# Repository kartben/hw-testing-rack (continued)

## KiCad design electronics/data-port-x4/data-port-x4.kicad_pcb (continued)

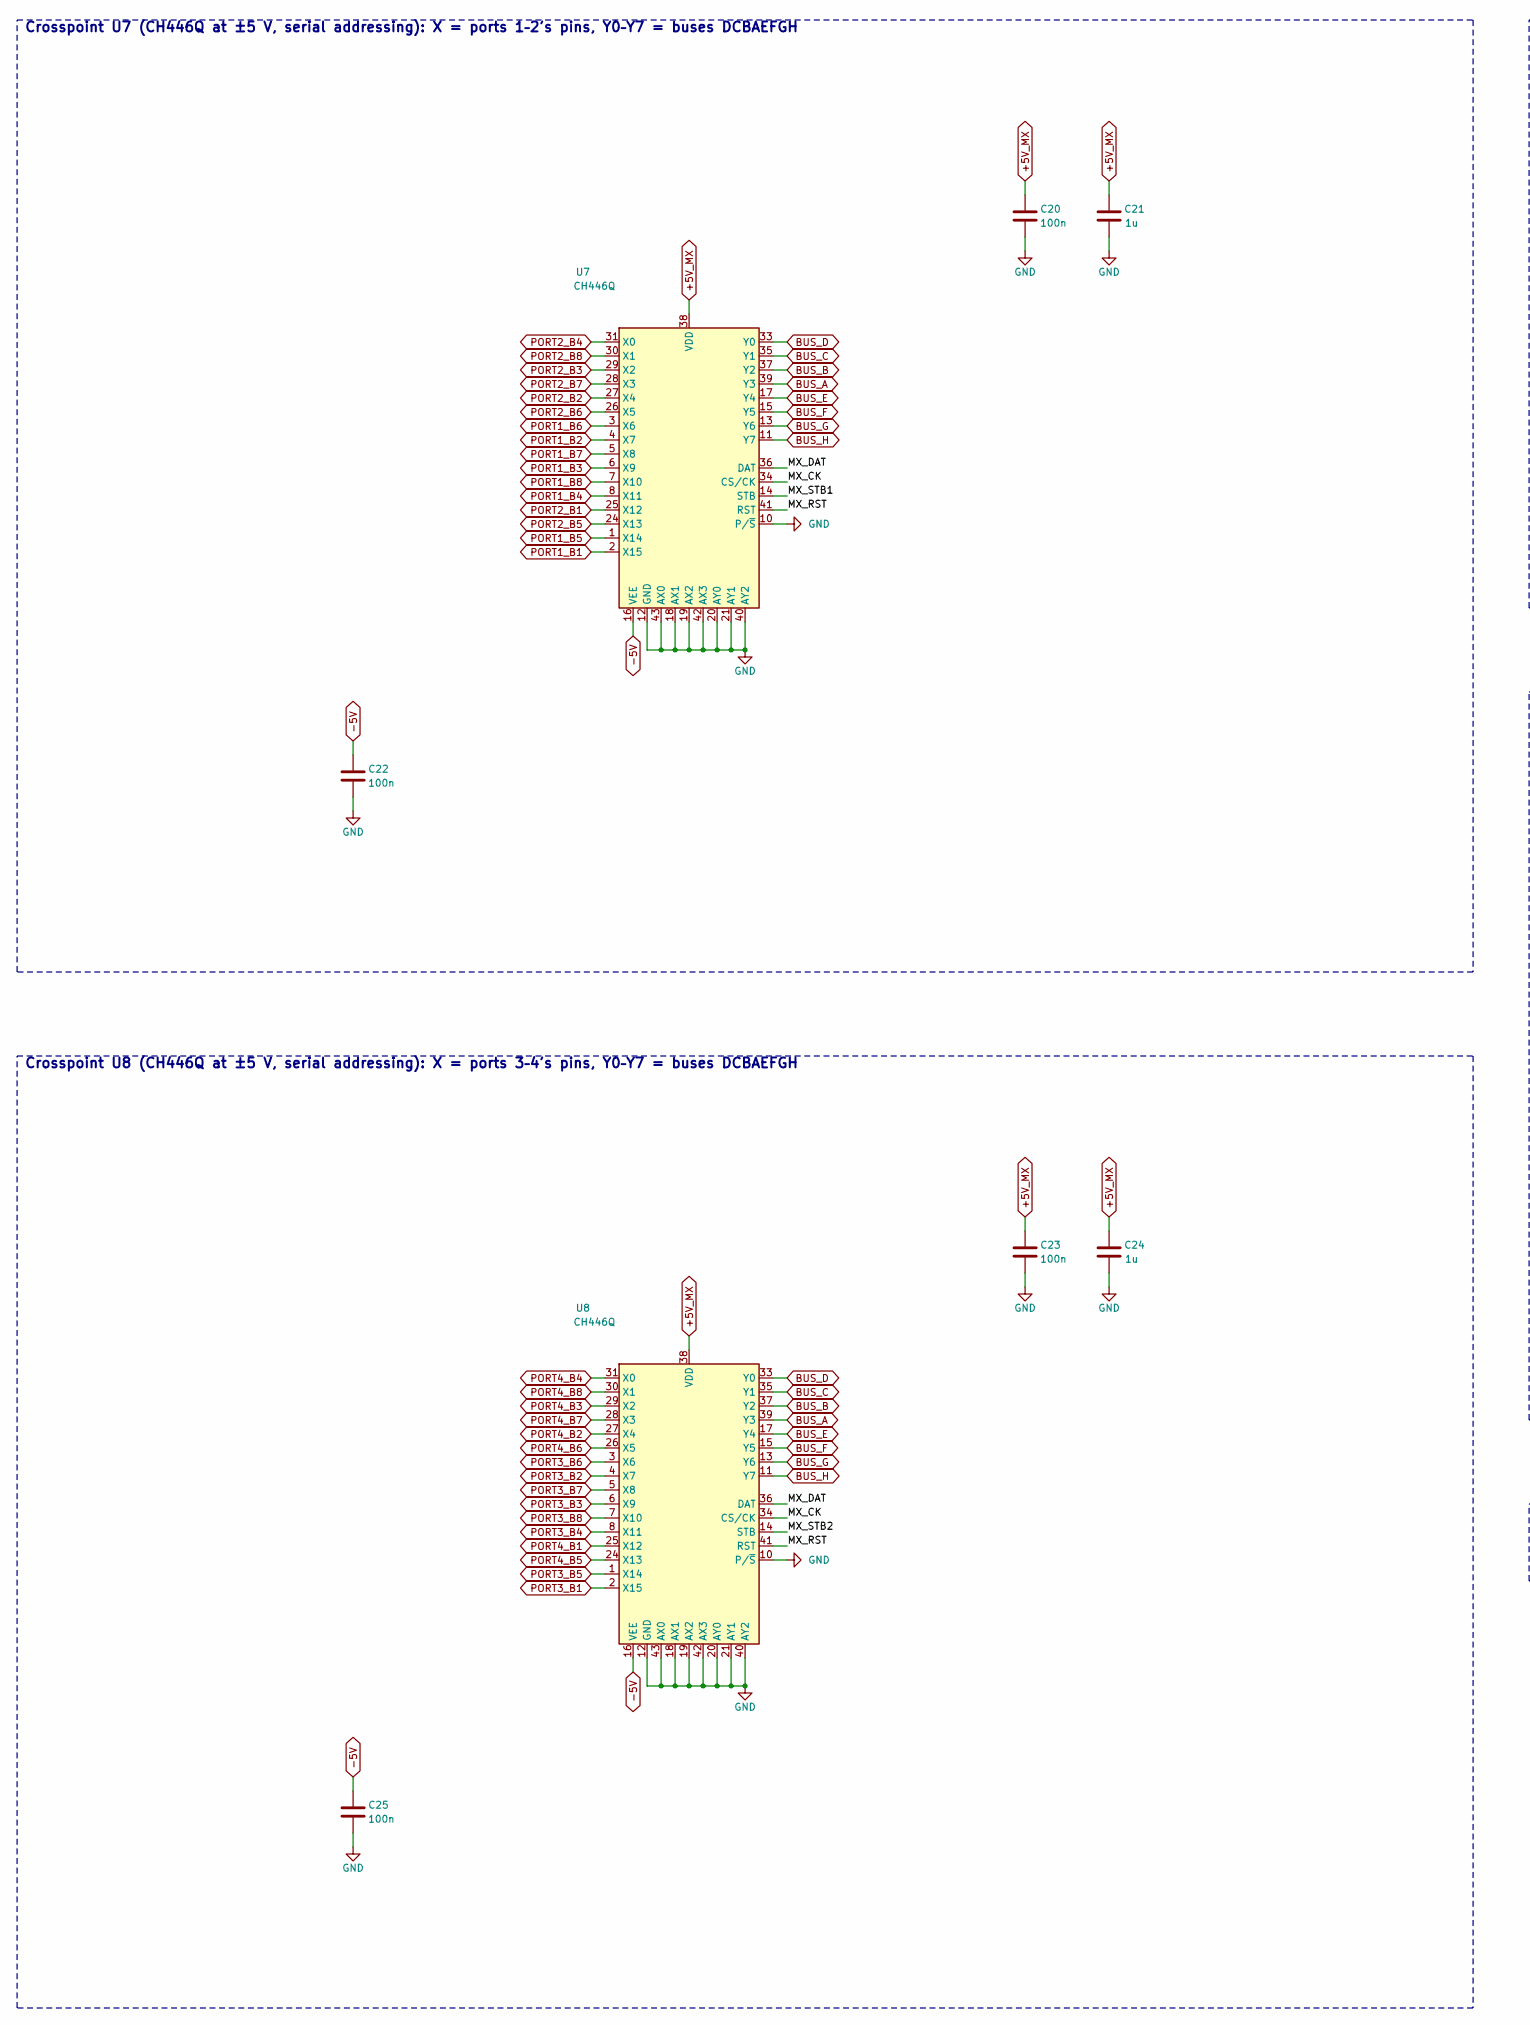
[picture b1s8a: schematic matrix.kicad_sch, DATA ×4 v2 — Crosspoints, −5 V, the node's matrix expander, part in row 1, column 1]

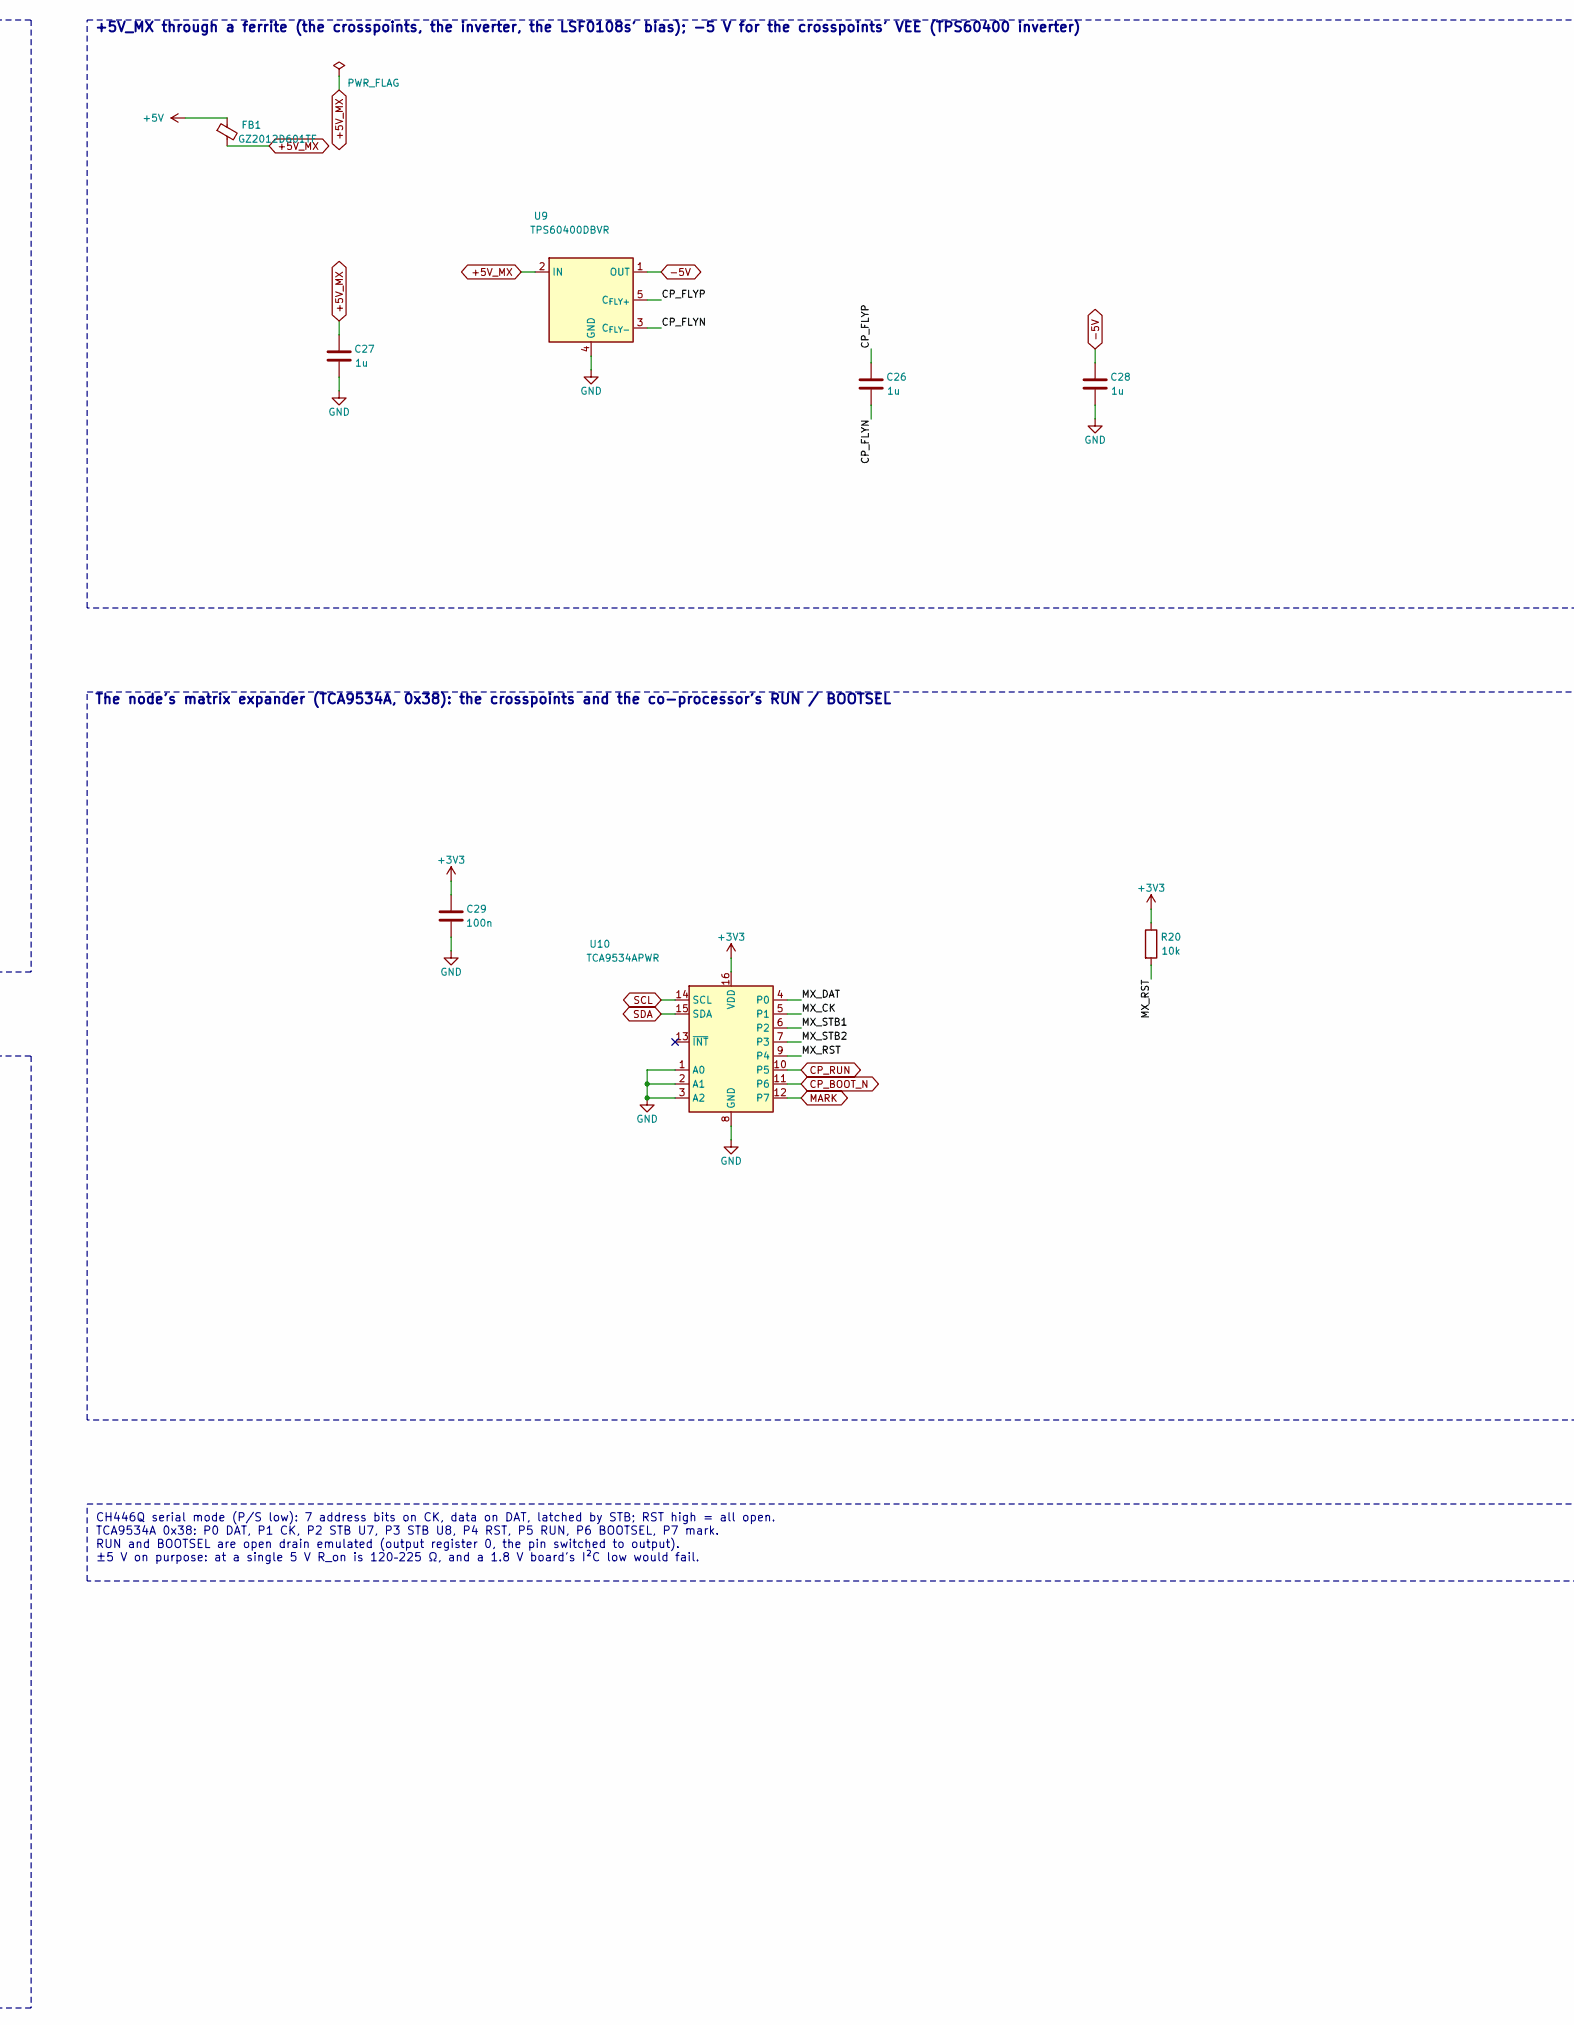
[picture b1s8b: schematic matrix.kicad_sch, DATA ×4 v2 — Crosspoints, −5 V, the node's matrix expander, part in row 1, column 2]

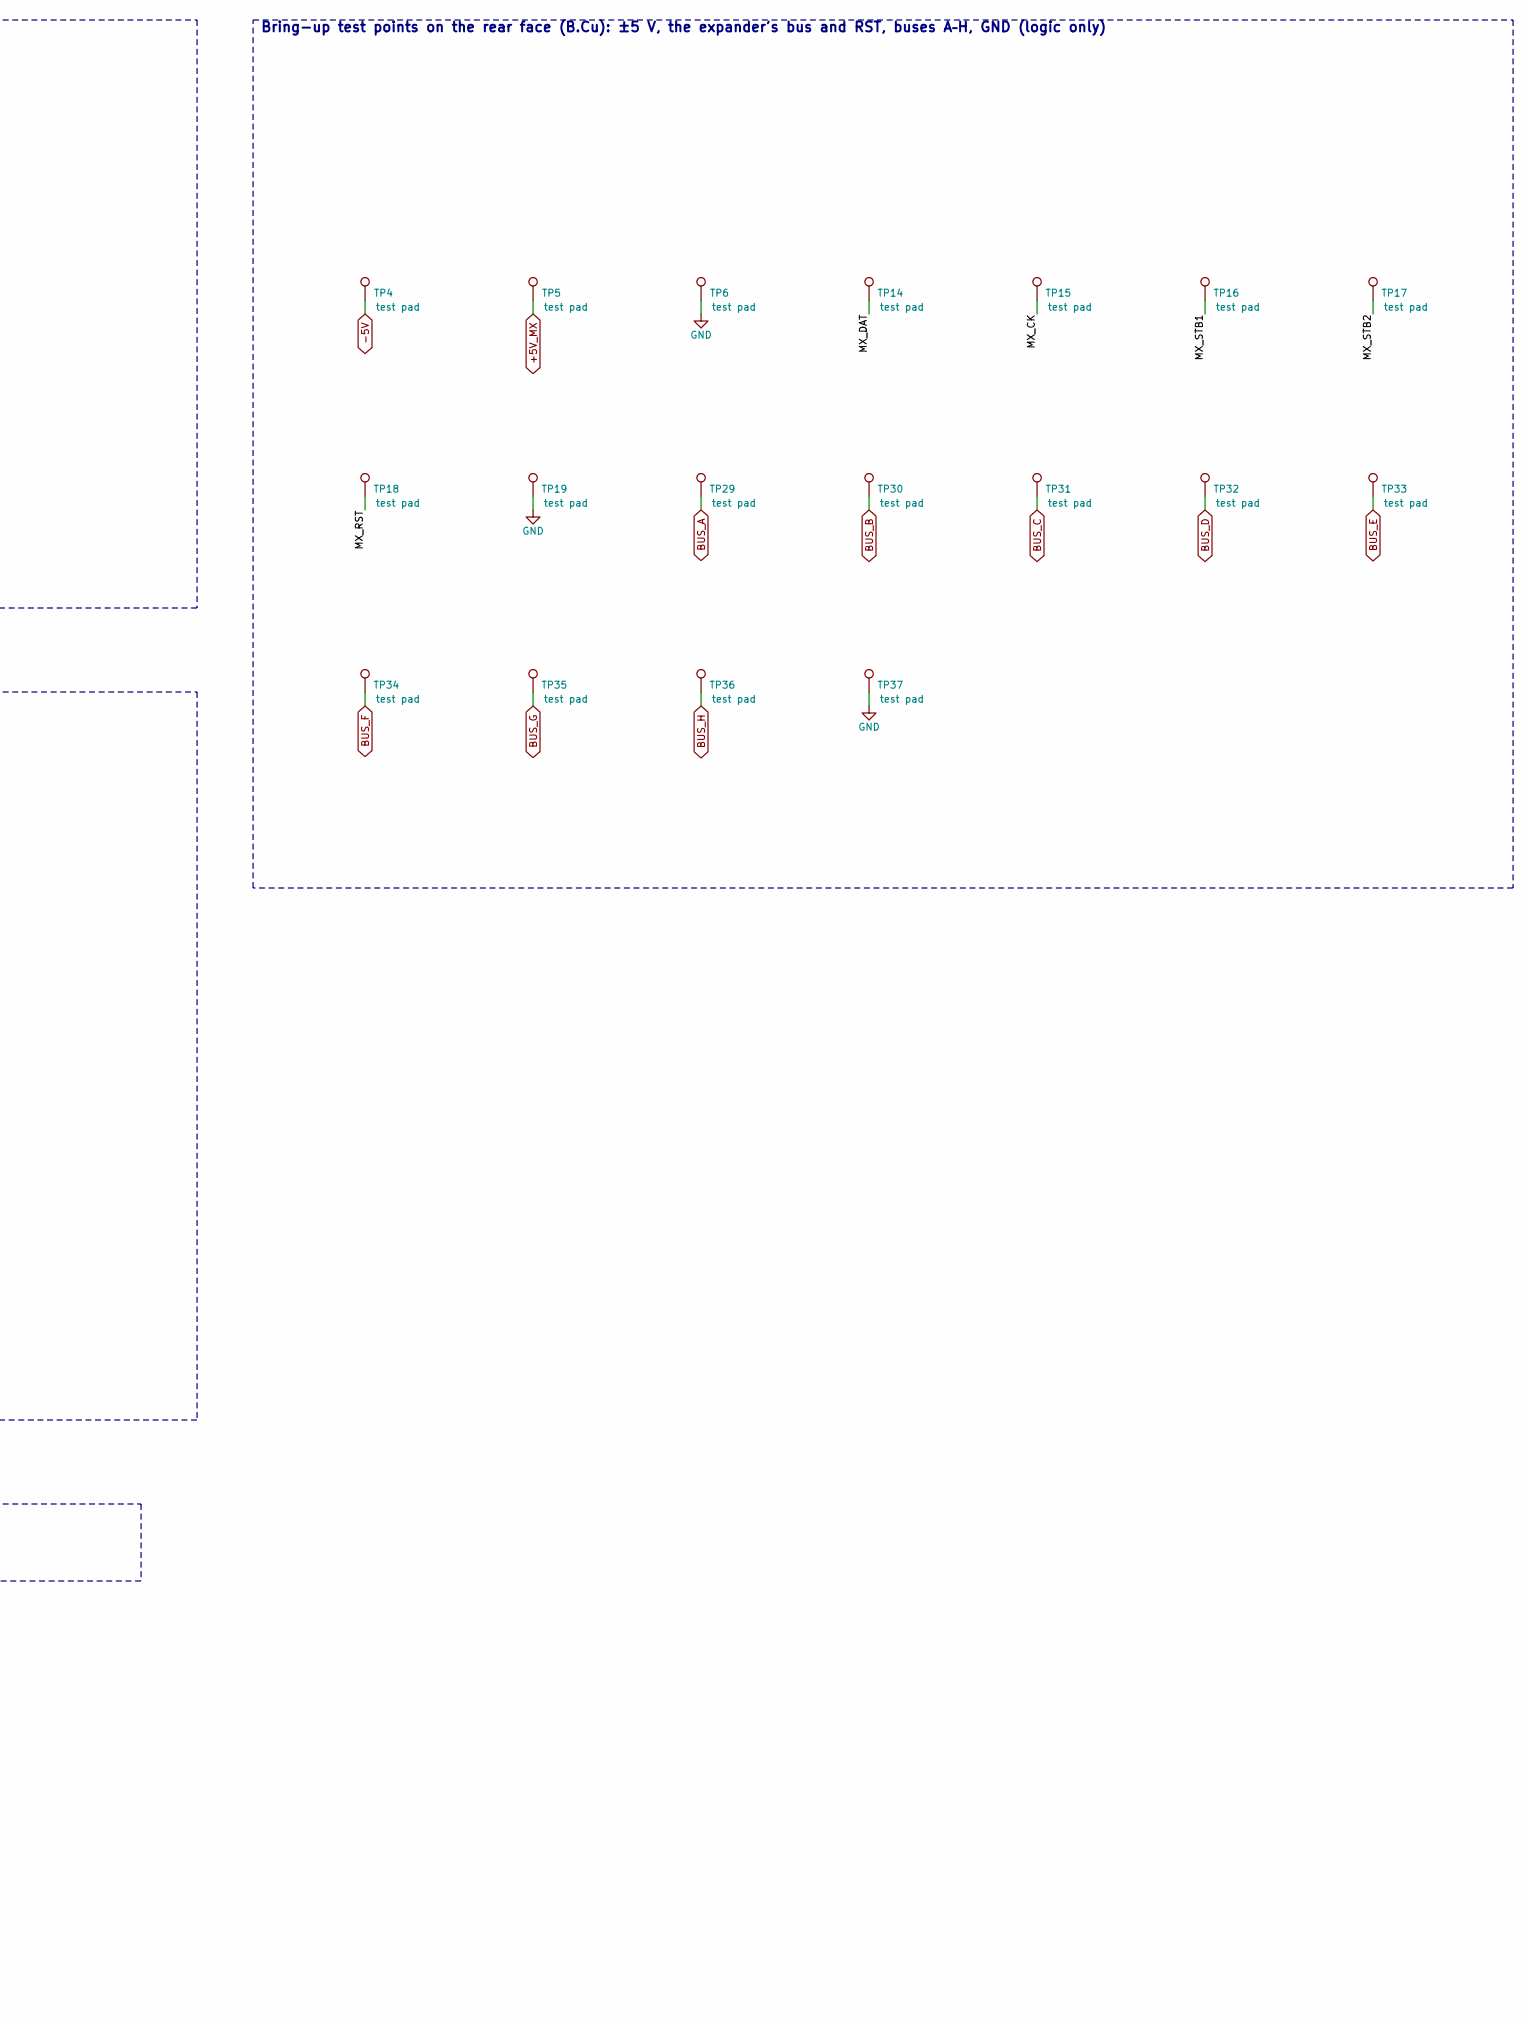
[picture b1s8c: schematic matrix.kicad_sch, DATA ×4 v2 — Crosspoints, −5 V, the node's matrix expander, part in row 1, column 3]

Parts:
C20, C22, C23, C25, C29: 100n; C_0402_1005Metric; MPN CL05B104KO5NNNC; LCSC C1525
C21, C24, C26, C27, C28: 1u; C_0402_1005Metric; MPN CL05A105KA5NQNC; LCSC C52923
FB1: GZ2012D601TF; L_0805_2012Metric; MPN GZ2012D601TF; LCSC C1017
R20: 10k; R_0402_1005Metric; MPN 0402WGF1002TCE; LCSC C25744
TP4, TP5, TP6, TP19, TP37: test pad; TestPoint_Pad_D1.5mm; MPN test pad
TP14, TP15, TP16, TP17, TP18, TP29, TP30, TP31, TP32, TP33, TP34, TP35, TP36: test pad; TestPoint_Pad_D1.0mm; MPN test pad
U7, U8: CH446Q; LQFP-44_10x10mm_P0.8mm; MPN CH446Q; LCSC C109471
U9: TPS60400DBVR; SOT-23-5; MPN TPS60400DBVR; LCSC C9839
U10: TCA9534APWR; TSSOP-16_4.4x5mm_P0.65mm; MPN TCA9534APWR; LCSC C206010

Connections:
+3V3: C29.1, R20.1, U10.16 (VDD); also elsewhere on the board
+5V: FB1.1; also elsewhere on the board
+5V_MX: C20.1, C21.1, C23.1, C24.1, C27.1, FB1.2, TP5.1, U7.38 (VDD), U8.38 (VDD), U9.2 (IN); also elsewhere on the board
-5V: C22.1, C25.1, C28.1, TP4.1, U7.16 (VEE), U8.16 (VEE), U9.1 (OUT); also elsewhere on the board
/Matrix/CP_FLYN: C26.2, U9.3 (C_{FLY-})
/Matrix/CP_FLYP: C26.1, U9.5 (C_{FLY+})
/Matrix/MX_CK: TP15.1, U7.34 (CS/CK), U8.34 (CS/CK), U10.5 (P1)
/Matrix/MX_DAT: TP14.1, U7.36 (DAT), U8.36 (DAT), U10.4 (P0)
/Matrix/MX_RST: R20.2, TP18.1, U7.41 (RST), U8.41 (RST), U10.9 (P4)
/Matrix/MX_STB1: TP16.1, U7.14 (STB), U10.6 (P2)
/Matrix/MX_STB2: TP17.1, U8.14 (STB), U10.7 (P3)
BUS_A: TP29.1, U7.39 (Y3), U8.39 (Y3); also elsewhere on the board
BUS_B: TP30.1, U7.37 (Y2), U8.37 (Y2); also elsewhere on the board
BUS_C: TP31.1, U7.35 (Y1), U8.35 (Y1); also elsewhere on the board
BUS_D: TP32.1, U7.33 (Y0), U8.33 (Y0); also elsewhere on the board
BUS_E: TP33.1, U7.17 (Y4), U8.17 (Y4); also elsewhere on the board
BUS_F: TP34.1, U7.15 (Y5), U8.15 (Y5); also elsewhere on the board
BUS_G: TP35.1, U7.13 (Y6), U8.13 (Y6); also elsewhere on the board
BUS_H: TP36.1, U7.11 (Y7), U8.11 (Y7); also elsewhere on the board
CP_BOOT_N: U10.11 (P6); also elsewhere on the board
CP_RUN: U10.10 (P5); also elsewhere on the board
GND: C20.2, C21.2, C22.2, C23.2, C24.2, C25.2, C27.2, C28.2, C29.2, TP6.1, TP19.1, TP37.1, U7.10 (P/~S), U7.12 (GND), U7.18 (AX1), U7.19 (AX2), U7.20 (AY0), U7.21 (AY1), U7.40 (AY2), U7.42 (AX3), U7.43 (AX0), U8.10 (P/~S), U8.12 (GND), U8.18 (AX1), U8.19 (AX2), U8.20 (AY0), U8.21 (AY1), U8.40 (AY2), U8.42 (AX3), U8.43 (AX0), U9.4 (GND), U10.1 (A0), U10.2 (A1), U10.3 (A2), U10.8 (GND); also elsewhere on the board
MARK: U10.12 (P7); also elsewhere on the board
PORT1_B1: U7.2 (X15); also elsewhere on the board
PORT1_B2: U7.4 (X7); also elsewhere on the board
PORT1_B3: U7.6 (X9); also elsewhere on the board
PORT1_B4: U7.8 (X11); also elsewhere on the board
PORT1_B5: U7.1 (X14); also elsewhere on the board
PORT1_B6: U7.3 (X6); also elsewhere on the board
PORT1_B7: U7.5 (X8); also elsewhere on the board
PORT1_B8: U7.7 (X10); also elsewhere on the board
PORT2_B1: U7.25 (X12); also elsewhere on the board
PORT2_B2: U7.27 (X4); also elsewhere on the board
PORT2_B3: U7.29 (X2); also elsewhere on the board
PORT2_B4: U7.31 (X0); also elsewhere on the board
PORT2_B5: U7.24 (X13); also elsewhere on the board
PORT2_B6: U7.26 (X5); also elsewhere on the board
PORT2_B7: U7.28 (X3); also elsewhere on the board
PORT2_B8: U7.30 (X1); also elsewhere on the board
PORT3_B1: U8.2 (X15); also elsewhere on the board
PORT3_B2: U8.4 (X7); also elsewhere on the board
PORT3_B3: U8.6 (X9); also elsewhere on the board
PORT3_B4: U8.8 (X11); also elsewhere on the board
PORT3_B5: U8.1 (X14); also elsewhere on the board
PORT3_B6: U8.3 (X6); also elsewhere on the board
PORT3_B7: U8.5 (X8); also elsewhere on the board
PORT3_B8: U8.7 (X10); also elsewhere on the board
PORT4_B1: U8.25 (X12); also elsewhere on the board
PORT4_B2: U8.27 (X4); also elsewhere on the board
PORT4_B3: U8.29 (X2); also elsewhere on the board
PORT4_B4: U8.31 (X0); also elsewhere on the board
PORT4_B5: U8.24 (X13); also elsewhere on the board
PORT4_B6: U8.26 (X5); also elsewhere on the board
PORT4_B7: U8.28 (X3); also elsewhere on the board
PORT4_B8: U8.30 (X1); also elsewhere on the board
SCL: U10.14 (SCL); also elsewhere on the board
SDA: U10.15 (SDA); also elsewhere on the board

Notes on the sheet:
Crosspoint U7 (CH446Q at ±5 V, serial addressing): X = ports 1–2's pins, Y0–Y7 = buses DCBAEFGH
Crosspoint U8 (CH446Q at ±5 V, serial addressing): X = ports 3–4's pins, Y0–Y7 = buses DCBAEFGH
+5V_MX through a ferrite (the crosspoints, the inverter, the LSF0108s' bias); −5 V for the crosspoints' VEE (TPS60400 inverter)
The node's matrix expander (TCA9534A, 0x38): the crosspoints and the co-processor's RUN / BOOTSEL
Bring-up test points on the rear face (B.Cu): ±5 V, the expander's bus and RST, buses A–H, GND (logic only)
CH446Q serial mode (P/S low): 7 address bits on CK, data on DAT, latched by STB; RST high = all open. TCA9534A 0x38: P0 DAT, P1 CK, P2 STB U7, P3 STB U8, P4 RST, P5 RUN, P6 BOOTSEL, P7 mark. RUN and BOOTSEL are open drain emulated (output register 0, the pin switched to output). ±5 V on purpose: at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

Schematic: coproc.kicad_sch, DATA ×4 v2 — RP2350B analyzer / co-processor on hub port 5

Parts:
C31, C34, C47: 4.7u; C_0402_1005Metric; MPN CL05A475MP5NRNC; LCSC C23733
C32, C33: 4.7u; C_0402_1005Metric_RP; MPN CL05A475MP5NRNC; LCSC C23733
C35, C36, C37, C38, C39, C40, C41, C42, C43, C44, C45, C46: 100n; C_0402_1005Metric; MPN CL05B104KO5NNNC; LCSC C1525
C48, C49: 15p; C_0402_1005Metric; MPN 0402CG150J500NT; LCSC C1548
D1: KT-0805G; LED_0805_2012Metric; MPN KT-0805G; LCSC C2297
FB2: GZ2012D601TF; L_0805_2012Metric; MPN GZ2012D601TF; LCSC C1017
J2: SWD; PinHeader_1x05_P2.54mm_Vertical; MPN HX PZ2.54-1x5P ZZ; LCSC C32713271
L1: AOTA-B201610S3R3-101-T; L_Abracon_AOTA-B201610; MPN AOTA-B201610S3R3-101-T; LCSC C42411119
R21: 33; R_0402_1005Metric; MPN 0402WGF330JTCE; LCSC C25105
R22, R26, R27: 1k; R_0402_1005Metric; MPN 0402WGF1001TCE; LCSC C11702
R23, R24: 27; R_0402_1005Metric; MPN 0402WGF270JTCE; LCSC C25100
R25, R40: 10k; R_0402_1005Metric; MPN 0402WGF1002TCE; LCSC C25744
R38, R41: 100k; R_0402_1005Metric; MPN 0402WGF1003TCE; LCSC C25741
R39: 47k; R_0402_1005Metric; MPN 0402WGF4702TCE; LCSC C25792
RN6, RN7: 2.2k; R_Array_Convex_4x0402; MPN 4D02WGJ0222TCE; LCSC C26075
RN8, RN9: 10k; R_Array_Convex_4x0402; MPN 4D02WGJ0103TCE; LCSC C25725
TP1, TP2, TP12, TP13: test pad; TestPoint_Pad_D1.0mm; MPN test pad
TP3, TP10, TP11: test pad; TestPoint_Pad_D1.5mm; MPN test pad
U11: RP2350B; QFN-80-1EP_10x10mm_P0.4mm_EP3.4x3.4mm; MPN RP2350B; LCSC C42415655
Y2: ABM8-272-T3; Crystal_SMD_3225-4Pin_3.2x2.5mm; MPN ABM8-272-T3; LCSC C20625731

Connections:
+3V3: FB2.1, J2.5, RN8.5 (R4.2), RN8.6 (R3.2), RN8.7 (R2.2), RN8.8 (R1.2), RN9.5 (R4.2), RN9.6 (R3.2), RN9.7 (R2.2), RN9.8 (R1.2); also elsewhere on the board
+5V_MX: R38.1; also elsewhere on the board
-5V: R41.2; also elsewhere on the board
/Co-processor/+1V1: C33.1, C45.1, C46.1, C47.1, L1.1, TP11.1, U11.10 (DVDD), U11.32 (DVDD), U11.51 (DVDD), U11.65 (VREG_FB)
/Co-processor/+3V3_CP: C31.1, C32.1, C35.1, C36.1, C37.1, C38.1, C39.1, C40.1, C41.1, C42.1, C43.1, C44.1, FB2.2, R21.1, R25.1, R40.1, TP10.1, U11.5 (IOVDD), U11.15 (IOVDD), U11.24 (IOVDD), U11.29 (IOVDD), U11.41 (IOVDD), U11.50 (IOVDD), U11.59 (ADC_AVDD), U11.60 (IOVDD), U11.64 (VREG_VIN), U11.68 (USB_OTP_VDD), U11.69 (QSPI_IOVDD), U11.76 (IOVDD)
/Co-processor/CP_DN: R24.1, U11.66 (USB_DM)
/Co-processor/CP_DP: R23.1, U11.67 (USB_DP)
/Co-processor/CP_LED: R27.1, U11.26 (GPIO25)
/Co-processor/CP_LED_A: D1.2 (A), R27.2
/Co-processor/CP_PU_A: RN6.1 (R1.1), U11.19 (GPIO19)
/Co-processor/CP_PU_B: RN6.2 (R2.1), U11.18 (GPIO18)
/Co-processor/CP_PU_C: RN6.3 (R3.1), U11.17 (GPIO17)
/Co-processor/CP_PU_D: RN6.4 (R4.1), U11.16 (GPIO16)
/Co-processor/CP_PU_E: RN7.1 (R1.1), U11.12 (GPIO13)
/Co-processor/CP_PU_F: RN7.2 (R2.1), U11.11 (GPIO12)
/Co-processor/CP_PU_G: RN7.3 (R3.1), U11.9 (GPIO11)
/Co-processor/CP_PU_H: RN7.4 (R4.1), U11.8 (GPIO10)
/Co-processor/CP_QSPI_SS: R26.2, U11.75 (~QSPI_SS)
/Co-processor/CP_SNS_5V: R38.2, R39.1, U11.55 (GPIO44/ADC4)
/Co-processor/CP_SNS_N5V: R40.2, R41.1, U11.56 (GPIO45/ADC5)
/Co-processor/CP_SWCLK: J2.1, TP1.1, U11.33 (SWCLK)
/Co-processor/CP_SWDIO: J2.3, TP2.1, U11.34 (SWDIO)
/Co-processor/CP_TRIG: U11.77 (GPIO0), U11.78 (GPIO1)
/Co-processor/CP_VREG_AVDD: C34.1, R21.2, U11.61 (VREG_AVDD)
/Co-processor/CP_VREG_LX: L1.2, U11.63 (VREG_LX)
/Co-processor/CP_XIN: C48.1, U11.30 (XIN), Y2.1
/Co-processor/CP_XOUT: R22.1, U11.31 (XOUT)
/Co-processor/CP_XTAL: C49.1, R22.2, Y2.3
BUS_A: RN6.8 (R1.2), RN8.1 (R1.1), U11.79 (GPIO2); also elsewhere on the board
BUS_B: RN6.7 (R2.2), RN8.2 (R2.1), U11.80 (GPIO3); also elsewhere on the board
BUS_C: RN6.6 (R3.2), RN8.3 (R3.1), U11.1 (GPIO4); also elsewhere on the board
BUS_D: RN6.5 (R4.2), RN8.4 (R4.1), U11.2 (GPIO5); also elsewhere on the board
BUS_E: RN7.8 (R1.2), RN9.1 (R1.1), U11.3 (GPIO6); also elsewhere on the board
BUS_F: RN7.7 (R2.2), RN9.2 (R2.1), U11.4 (GPIO7); also elsewhere on the board
BUS_G: RN7.6 (R3.2), RN9.3 (R3.1), U11.6 (GPIO8); also elsewhere on the board
BUS_H: RN7.5 (R4.2), RN9.4 (R4.1), U11.7 (GPIO9); also elsewhere on the board
CP_ADC1: U11.49 (GPIO40/ADC0); also elsewhere on the board
CP_ADC2: U11.54 (GPIO43/ADC3); also elsewhere on the board
CP_ADC3: U11.53 (GPIO42/ADC2); also elsewhere on the board
CP_ADC4: U11.52 (GPIO41/ADC1); also elsewhere on the board
CP_BOOT_N: R26.1, TP13.1; also elsewhere on the board
CP_HUB_DN: R24.2; also elsewhere on the board
CP_HUB_DP: R23.2; also elsewhere on the board
CP_RUN: J2.4, R25.2, TP12.1, U11.35 (RUN); also elsewhere on the board
GND: C31.2, C32.2, C33.2, C34.2, C35.2, C36.2, C37.2, C38.2, C39.2, C40.2, C41.2, C42.2, C43.2, C44.2, C45.2, C46.2, C47.2, C48.2, C49.2, D1.1 (K), J2.2, R39.2, TP3.1, U11.62 (VREG_PGND), U11.81 (GND), Y2.2 (G), Y2.4 (G); also elsewhere on the board
MARK: U11.13 (GPIO14); also elsewhere on the board

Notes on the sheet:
RP2350B, wired like a Pico 2 less its flash (the analyzer loaded into SRAM at power-up); its decoupling
Its 3.3 V from +3V3 through a ferrite, the core regulator as Raspberry Pi lays it out (3.3 µH, 3 × 4.7 µF, 33 Ω)
12 MHz crystal (ABM8-272-T3, 15 pF, 1k on XOUT), USB on hub port 5 (27 Ω), RUN, BOOTSEL, LED, SWD
Bring-up test points on the rear face (B.Cu): SWD, RUN, BOOTSEL, its rails, GND (logic only)
SWD header (J2, 1 × 5 through-hole, fitted by hand): the Debug Probe on 1–3, RUN and VTref for others
Bus pull-ups: 10k to 3.3 V always (the LSFs' B side), 2.2k switched by the co-processor (GPIO10–13, 16–19); the ±5 V rails into the ADC
GPIO2–9 = buses A–H (gusmanb CH1–8, 8-bit mode); GPIO0 → GPIO1 bridged (its trigger path). GPIO14 = the node's mark (TCA9534A P7); GPIO25 = LED; GPIO19…16, 13…10 = pull-up enables A…H (2.2k); GPIO40, 43, 42, 41 = VREF 1–4 / 2 (through 100k); GPIO44 = +5V × 47/147; GPIO45 = 3.3 V − (3.3 + 5) × 10/11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

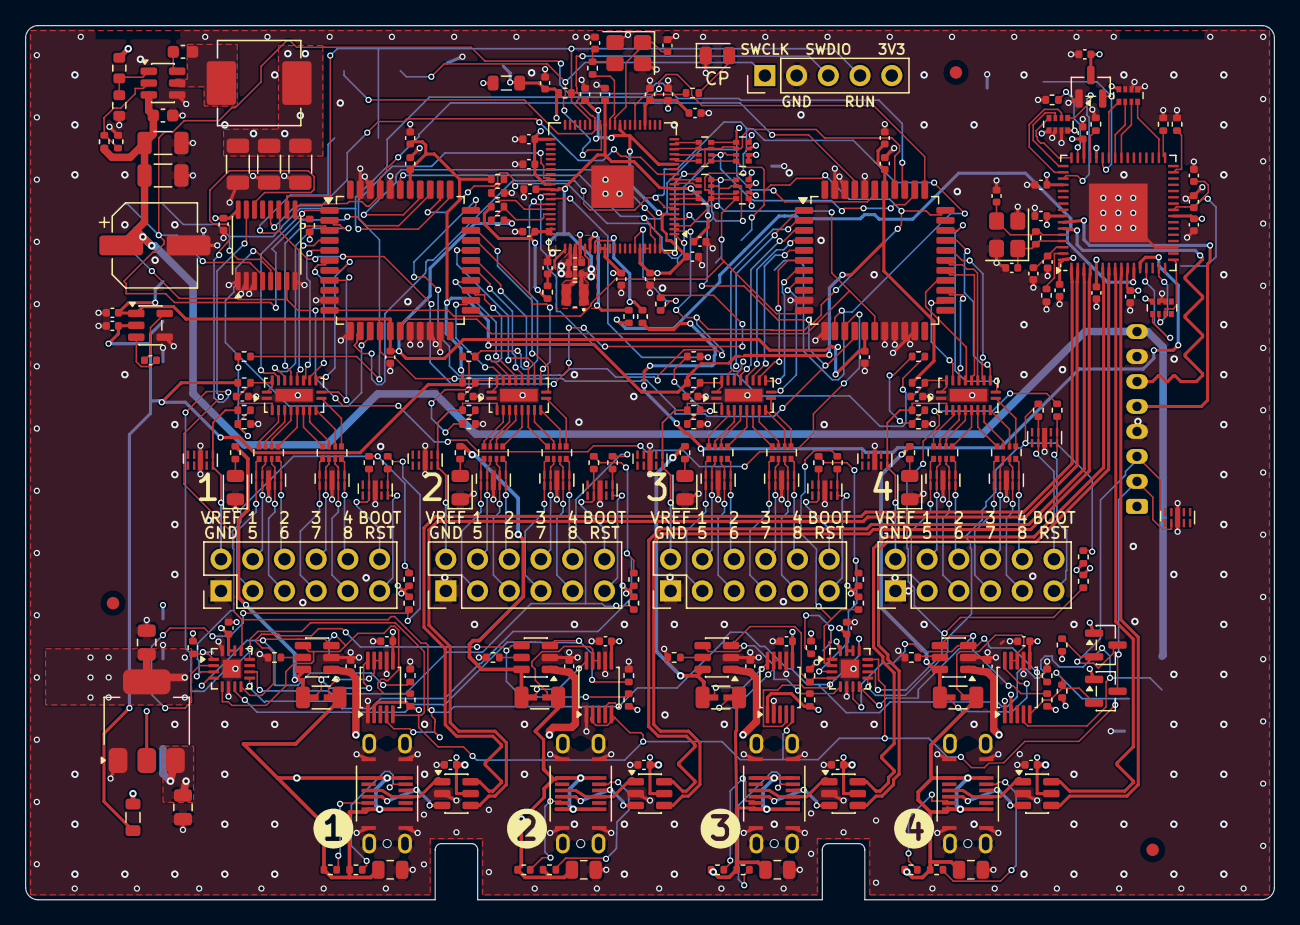
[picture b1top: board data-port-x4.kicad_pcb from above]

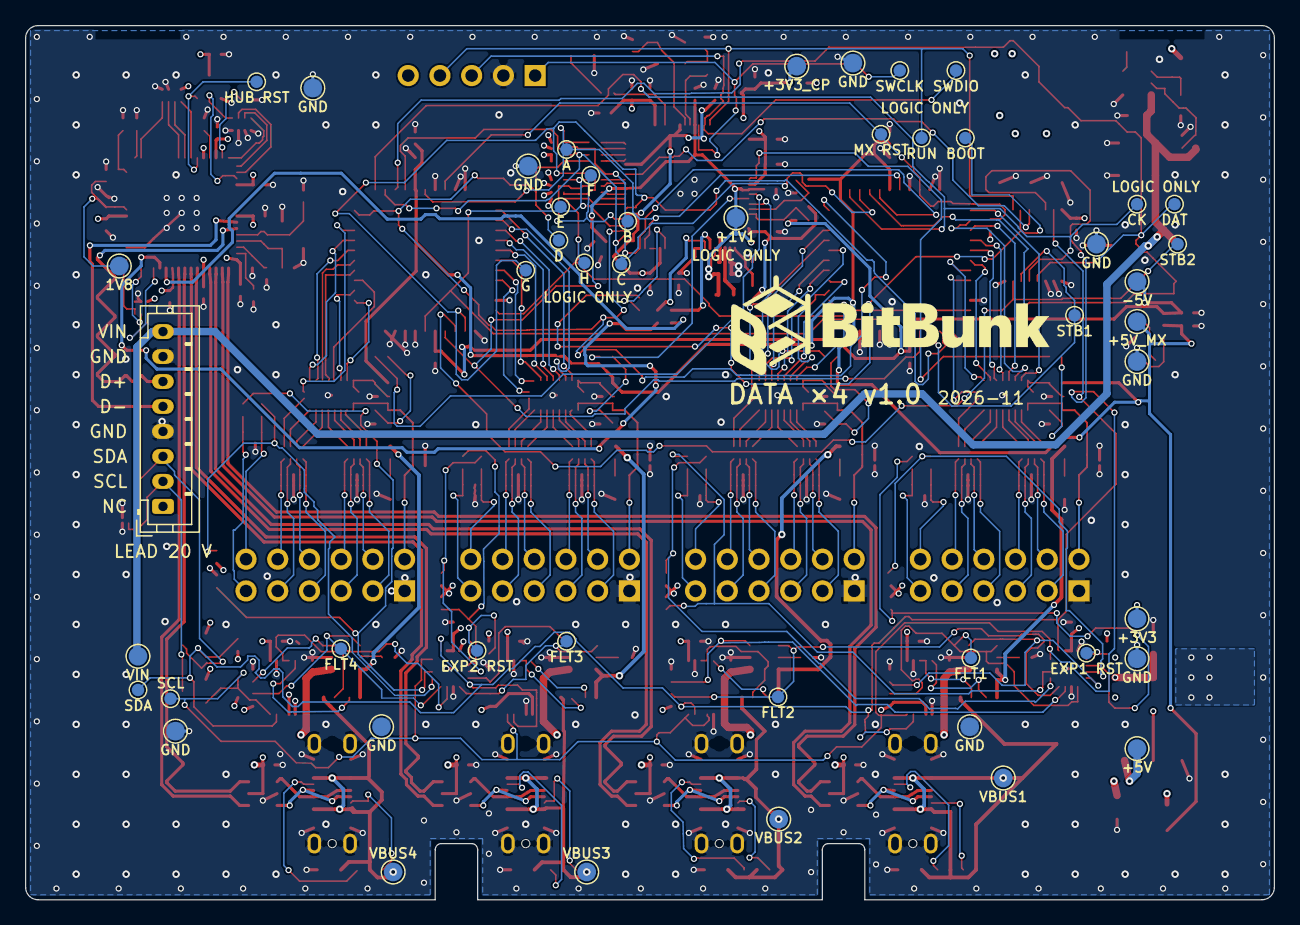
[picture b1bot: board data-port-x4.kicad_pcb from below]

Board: 4 copper layers, 100.0 x 70.0 mm, 293 parts (48 on the bottom side), 268 nets.

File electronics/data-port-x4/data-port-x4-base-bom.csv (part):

Designator,Qty,Value,Footprint,MPN,Manufacturer,LCSC,Description,DNP,Alternative,Assembly
"C2,C3,C102,C202,C302,C402",6,22u,C_0805_2012Metric,CL21A226MAQNNNE,Samsung Electro-Mechanics,C45783,Capacitor 22u 0805,,,
"C4,C5",2,33p,C_0402_1005Metric,0402CG330J500NT,FH (Guangdong Fenghua Advanced Tech),C1562,Capacitor 33p 0402,,,
"C6,C9,C10,C11,C12,C13,C14,C15,C16,C17,C18,C19,C103,C104,C203,C204,C303,C304,C403,C404",20,100n,C_0402_1005Metric,CL05B104KO5NNNC,Samsung Electro-Mechanics,C1525,Capacitor 100n 0402,,,
"C7,C8",2,4.7u,C_0402_1005Metric,CL05A475MP5NRNC,Samsung Electro-Mechanics,C23733,Capacitor 4.7u 0402,,,
"C20,C22,C23,C25,C29,C35,C36,C37,C38,C39,C40,C41,C42,C43,C44,C45,C46,C105,C205,C305,C405",21,100n,C_0402_1005Metric,CL05B104KO5NNNC,Samsung Electro-Mechanics,C1525,Capacitor 100n 0402,yes,,
"C21,C24,C26,C27,C28",5,1u,C_0402_1005Metric,CL05A105KA5NQNC,Samsung Electro-Mechanics,C52923,Capacitor 1u 0402,yes,,
"C31,C34,C47",3,4.7u,C_0402_1005Metric,CL05A475MP5NRNC,Samsung Electro-Mechanics,C23733,Capacitor 4.7u 0402,yes,,
"C32,C33",2,4.7u,C_0402_1005Metric_RP,CL05A475MP5NRNC,Samsung Electro-Mechanics,C23733,Capacitor 4.7u 0402,yes,,
"C48,C49",2,15p,C_0402_1005Metric,0402CG150J500NT,FH (Guangdong Fenghua Advanced Tech),C1548,Capacitor 15p 0402,yes,,
C60,1,33u,CP_Elec_6.3x7.7,VH1H330ME077000CE0,Changzhou Huawei Electronics,C240518,"33 µF 50 V aluminium electrolytic, 6.3 × 7.7 mm",,"Panasonic EEEFK1H330XP (C344076): 33 µF 50 V, 6.3 × 7.7 mm, 146 mA at 120 Hz; RVT1H330M0607 (C72509, JLC Standard PCBA only)",
"C61,C62",2,10u,C_1206_3216Metric,CL31A106KBHNNNE,Samsung Electro-Mechanics,C13585,Capacitor 10u 1206,,,
"C63,C64",2,100n,C_0603_1608Metric,CC0603KRX7R9BB104,YAGEO,C14663,Capacitor 100n 0603,,,
"C65,C66,C67",3,22u,C_1206_3216Metric,CL31A226KAHNNNE,Samsung Electro-Mechanics,C12891,Capacitor 22u 1206,,,
"C101,C201,C301,C401",4,1u,C_0402_1005Metric,CL05A105KA5NQNC,Samsung Electro-Mechanics,C52923,Capacitor 1u 0402,,,
D1,1,KT-0805G,LED_0805_2012Metric,KT-0805G,Hubei KENTO,C2297,green LED 0805,yes,,
"D101,D201,D301,D401",4,KT-0805G,LED_0805_2012Metric,KT-0805G,Hubei KENTO,C2297,green LED 0805,,,
"FB1,FB2",2,GZ2012D601TF,L_0805_2012Metric,GZ2012D601TF,Sunlord,C1017,"ferrite bead 600 Ω @ 100 MHz, 500 mA, 0805",yes,,
J1,1,LEAD,JST_PH_B8B-PH-K_1x08_P2.00mm_Vertical,B8B-PH-K-S(LF)(SN),JST,C157974,"JST PH 8-pin, vertical, through-hole",,,"hand-solder, buy loose (LCSC)"
J2,1,SWD,PinHeader_1x05_P2.54mm_Vertical,HX PZ2.54-1x5P ZZ,hanxia,C32713271,"pin header 1 × 5, 2.54 mm, through-hole",yes,,"hand-solder, buy loose (LCSC)"
J101,1,PORT1,USB_C_Receptacle_GCT_USB4145-03-0170-C_Vertical,USB4145-03-0170-C,GCT,C5181332,"USB-C receptacle, USB 2.0, 16 pins, vertical (top mount, 7.46 mm), 5 A on VBUS, 1.70 mm shell stakes",,,
J102,1,PINS1,PinHeader_2x06_P2.54mm_Vertical,HX PZ2.54-2x6P ZZ,hanxia,C32713279,"pin header 2 × 6, 2.54 mm, through-hole, soldered by hand: Dupont jumpers to a DUT's pins",,,"hand-solder, buy loose (LCSC)"
J201,1,PORT2,USB_C_Receptacle_GCT_USB4145-03-0170-C_Vertical,USB4145-03-0170-C,GCT,C5181332,"USB-C receptacle, USB 2.0, 16 pins, vertical (top mount, 7.46 mm), 5 A on VBUS, 1.70 mm shell stakes",,,
J202,1,PINS2,PinHeader_2x06_P2.54mm_Vertical,HX PZ2.54-2x6P ZZ,hanxia,C32713279,"pin header 2 × 6, 2.54 mm, through-hole, soldered by hand: Dupont jumpers to a DUT's pins",,,"hand-solder, buy loose (LCSC)"
J301,1,PORT3,USB_C_Receptacle_GCT_USB4145-03-0170-C_Vertical,USB4145-03-0170-C,GCT,C5181332,"USB-C receptacle, USB 2.0, 16 pins, vertical (top mount, 7.46 mm), 5 A on VBUS, 1.70 mm shell stakes",,,
J302,1,PINS3,PinHeader_2x06_P2.54mm_Vertical,HX PZ2.54-2x6P ZZ,hanxia,C32713279,"pin header 2 × 6, 2.54 mm, through-hole, soldered by hand: Dupont jumpers to a DUT's pins",,,"hand-solder, buy loose (LCSC)"
J401,1,PORT4,USB_C_Receptacle_GCT_USB4145-03-0170-C_Vertical,USB4145-03-0170-C,GCT,C5181332,"USB-C receptacle, USB 2.0, 16 pins, vertical (top mount, 7.46 mm), 5 A on VBUS, 1.70 mm shell stakes",,,
J402,1,PINS4,PinHeader_2x06_P2.54mm_Vertical,HX PZ2.54-2x6P ZZ,hanxia,C32713279,"pin header 2 × 6, 2.54 mm, through-hole, soldered by hand: Dupont jumpers to a DUT's pins",,,"hand-solder, buy loose (LCSC)"
L1,1,AOTA-B201610S3R3-101-T,L_Abracon_AOTA-B201610,AOTA-B201610S3R3-101-T,Abracon LLC,C42411119,"3.3 µH 2.4 A molded inductor, 0806, polarity dot on pad 1 (RP2350 core regulator)",yes,"LCSC stock low (1 on 2026-10-19): JLC Global Sourcing; YSMC201612H-3R3MB (C41405891, unmarked polarity) only at our own risk, per Raspberry Pi",
L2,1,3.3u,L_Changjiang_FXL0630,IHLP2525CZER3R3M01,Vishay Intertech,C506574,"3.3 µH, 75 V, 13.5 A sat (−20 %), 6 A heat, 28 / 30 mΩ, molded",,,
"Q1,Q2",2,2N7002,SOT-23,2N7002,CJ,C8545,N-MOSFET 60 V (open-drain AUX outputs),,,
R1,1,12k,R_0402_1005Metric,0402WGF1202TCE,UNI-ROYAL(Uniroyal Elec),C25752,Resistor 12k 0402,,,
"R3,R4,R5,R9,R11,R12,R51,R102,R103,R202,R203,R302,R303,R402,R403",15,10k,R_0402_1005Metric,0402WGF1002TCE,UNI-ROYAL(Uniroyal Elec),C25744,Resistor 10k 0402,,,
"R6,R7",2,4.7k,R_0402_1005Metric,0402WGF4701TCE,UNI-ROYAL(Uniroyal Elec),C25900,Resistor 4.7k 0402,,,
R10,1,1M,R_0402_1005Metric,0402WGF1004TCE,UNI-ROYAL(Uniroyal Elec),C26083,Resistor 1M 0402,,,
"R20,R25,R40,R112,R113,R212,R213,R312,R313,R412,R413",11,10k,R_0402_1005Metric,0402WGF1002TCE,UNI-ROYAL(Uniroyal Elec),C25744,Resistor 10k 0402,yes,,
R21,1,33,R_0402_1005Metric,0402WGF330JTCE,UNI-ROYAL(Uniroyal Elec),C25105,Resistor 33 0402,yes,,
"R22,R26,R27",3,1k,R_0402_1005Metric,0402WGF1001TCE,UNI-ROYAL(Uniroyal Elec),C11702,Resistor 1k 0402,yes,,
"R23,R24",2,27,R_0402_1005Metric,0402WGF270JTCE,UNI-ROYAL(Uniroyal Elec),C25100,Resistor 27 0402,yes,,
"R38,R41,R115,R215,R315,R415",6,100k,R_0402_1005Metric,0402WGF1003TCE,UNI-ROYAL(Uniroyal Elec),C25741,Resistor 100k 0402,yes,,
R39,1,47k,R_0402_1005Metric,0402WGF4702TCE,UNI-ROYAL(Uniroyal Elec),C25792,Resistor 47k 0402,yes,,
"R50,R109,R110,R209,R210,R309,R310,R409,R410",9,100k,R_0402_1005Metric,0402WGF1003TCE,UNI-ROYAL(Uniroyal Elec),C25741,Resistor 100k 0402,,,
R52,1,100k,R_0603_1608Metric,0603WAF1003T5E,UNI-ROYAL(Uniroyal Elec),C25803,Resistor 100k 0603,,,
R53,1,18.7k,R_0603_1608Metric,0603WAF1872T5E,UNI-ROYAL(Uniroyal Elec),C22893,Resistor 18.7k 0603,,,
"R101,R201,R301,R401",4,45.3k,R_0402_1005Metric,FRC0402F4532TS,FOJAN,C2933099,Resistor 45.3k 0402,,,
"R104,R105,R204,R205,R304,R305,R404,R405",8,56k,R_0402_1005Metric,0402WGF5602TCE,UNI-ROYAL(Uniroyal Elec),C25796,Resistor 56k 0402,,,
"R106,R206,R306,R406",4,100m,R_1206_3216Metric_Kelvin,1206W4F100LT5E,UNI-ROYAL(Uniroyal Elec),C25334,"100 mΩ 1 % 0.25 W, as a current shunt",,,
"R107,R108,R114,R207,R208,R214,R307,R308,R314,R407,R408,R414",12,1k,R_0402_1005Metric,0402WGF1001TCE,UNI-ROYAL(Uniroyal Elec),C11702,Resistor 1k 0402,,,
"R111,R211,R311,R411",4,200k,R_0402_1005Metric,0402WGF2003TCE,UNI-ROYAL(Uniroyal Elec),C25764,Resistor 200k 0402,yes,,
"RN1,RN2,RN3",3,10k,R_Array_Convex_4x0402,4D02WGJ0103TCE,UNI-ROYAL(Uniroyal Elec),C25725,"4 × resistor array 0402, 5 %",,,
"RN6,RN7",2,2.2k,R_Array_Convex_4x0402,4D02WGJ0222TCE,UNI-ROYAL(Uniroyal Elec),C26075,"4 × resistor array 0402, 5 %",yes,,
"RN8,RN9",2,10k,R_Array_Convex_4x0402,4D02WGJ0103TCE,UNI-ROYAL(Uniroyal Elec),C25725,"4 × resistor array 0402, 5 %",yes,,
"RN101,RN102,RN201,RN202,RN301,RN302,RN401,RN402",8,100,R_Array_Convex_4x0402,4D02WGJ0101TCE,UNI-ROYAL(Uniroyal Elec),C48442,"4 × resistor array 0402, 5 %",yes,,
U1,1,USB2517I-JZX,QFN-64-1EP_9x9mm_P0.5mm_EP4.7x4.7mm_Paste4x4,USB2517I-JZX,Microchip Tech,C478081,"USB 2.0 hub, 7 ports, one transaction translator per port (MTT), industrial",,,
"U2,U6",2,TCA6408ARGTR,VQFN-16-1EP_3x3mm_P0.5mm_EP1.45x1.45mm,TCA6408ARGTR,Texas Instruments,C181499,"8-bit I2C I/O expander, 5.5 V tolerant I/O, open-drain INT",,,
U3,1,AP2114H-3.3TRG1,SOT-223-3_TabPin2,AP2114H-3.3TRG1,Diodes Incorporated,C150716,"3.3 V 1 A LDO, 450 mV dropout at 1 A, SOT-223",,,
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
